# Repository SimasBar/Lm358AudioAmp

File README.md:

# Stereo audio amp

Designed a simple audio amplifier using ICs that I had laying around.
Works surprisingly well up to 12V, although you need a clean power supply, otherwise you need additional filters on the power input side.

# Schematic

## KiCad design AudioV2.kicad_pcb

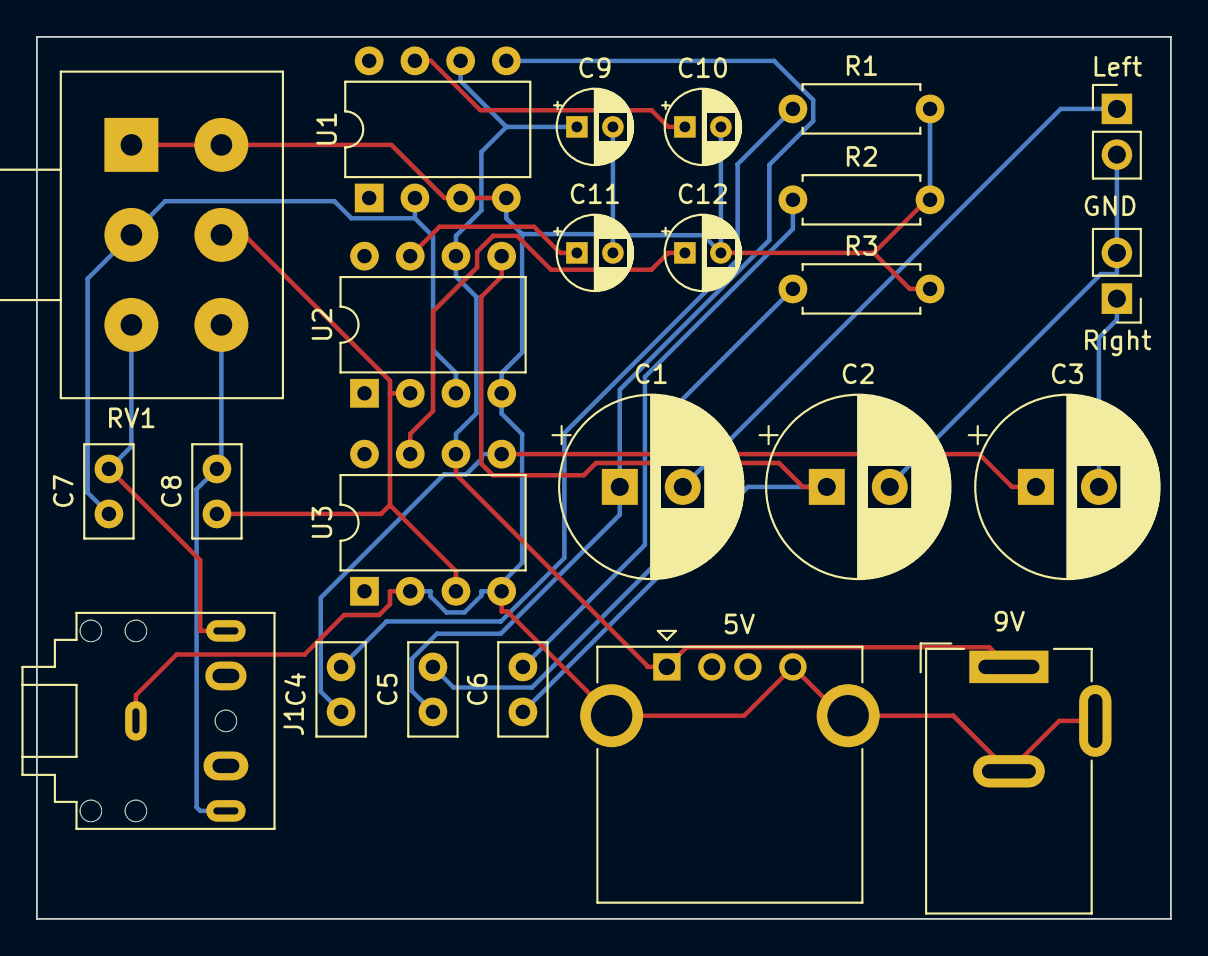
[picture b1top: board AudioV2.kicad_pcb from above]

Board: 2 copper layers, 63.0 x 49.0 mm, 24 parts (0 on the bottom side), 18 nets.

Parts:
5V: USB_A; USB_A_CONNFLY_DS1095-WNR0
9V: Barrel_Jack_Switch; BarrelJack_Wuerth_6941xx301002
C1, C2, C3: 1000uF; CP_Radial_D10.0mm_P3.50mm
C4, C5, C6: 0.1uF; C_Disc_D5.0mm_W2.5mm_P2.50mm
C7, C8: 47pF; C_Disc_D5.0mm_W2.5mm_P2.50mm
C9: 100uF; CP_Radial_D4.0mm_P2.00mm
C10, C11, C12: 10uF; CP_Radial_D4.0mm_P2.00mm
J1: AudioJack3; Jack_3.5mm_CUI_SJ1-3525N_Horizontal
Left: Left; PinHeader_1x02_P2.54mm_Vertical
R1, R2, R3: 10; R_Axial_DIN0207_L6.3mm_D2.5mm_P7.62mm_Horizontal
RV1: PotLog10K; Potentiometer_Alps_RK163_Dual_Horizontal
Right: Right; PinHeader_1x02_P2.54mm_Vertical
U1, U2, U3: LM386; DIP-8_W7.62mm

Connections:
GND: 5V.4 (GND), 5V.5 (Shield), 9V.2, 9V.3, C9.2, C10.2, C11.2, C12.2, J1.S, R1.2, R2.2, R3.2, RV1.1, RV1.4, U1.3 (+), U1.4 (GND), U2.4 (GND), U3.2 (-), U3.4 (GND)
unnamed: C1.1, C5.1, U1.5
unnamed: C1.2, Left.1
unnamed: C2.1, C6.1, U2.5
unnamed: C2.2, Left.2, Right.2
unnamed: C3.1, C4.1, U3.5
unnamed: C3.2, Right.1
unnamed: C4.2, R1.1
unnamed: C5.2, R3.1
unnamed: C6.2, R2.1
unnamed: C7.2, J1.R, RV1.3
unnamed: C8.2, J1.T, RV1.6
unnamed: 5V.1 (VBUS), 9V.1, C9.1, U1.6 (V+), U2.6 (V+), U3.6 (V+)
unnamed: C7.1, RV1.2, U1.2 (-), U2.3 (+)
unnamed: C10.1, U1.7 (BYPASS)
unnamed: C8.1, RV1.5, U2.2 (-), U3.3 (+)
unnamed: C11.1, U2.7 (BYPASS)
unnamed: C12.1, U3.7 (BYPASS)

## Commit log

2024-08-29 Labas pasauli
2024-08-29 schema
2024-08-30 Removed bloat
